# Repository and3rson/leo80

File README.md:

# leo80
Z80-based single-board computer

# Design considerations

- $0000-$7FFF - ROM.
- $8000-$FFFF - RAM.
- Address decoding with ATF16V8.
- Using perfboard for this, so trying to keep it small & simple - will be adding more fancy things later (LCD, UART, etc).
- Simple 8-bit input through '244 tri-state buffer.
- Simple 8-bit output through '273 flip-flop with 8 LEDs for visual output.
- I used AS6C4008 in schematic since it's included in Kicad parts by default. I have various SRAM chips available. Same with W27C512 EPROM.

# Schematic

# PCB

# Resources

- anycpu.org forum [thread](https://anycpu.org/forum/viewtopic.php?f=25&t=1060)
- Original [datasheet](https://www.zilog.com/docs/z80/um0080.pdf) (very slow download), or alternatively - archived versions on [my website](https://dun.ai/files/z80.pdf) and [archive.org](https://archive.org/details/um0080httpswww.zilog.comdocsz80um0080.pdf).
- Z80 interrupt vectors: https://www.smspower.org/Development/InterruptVectors
- SjASMPlus docs: https://z00m128.github.io/sjasmplus/documentation.html

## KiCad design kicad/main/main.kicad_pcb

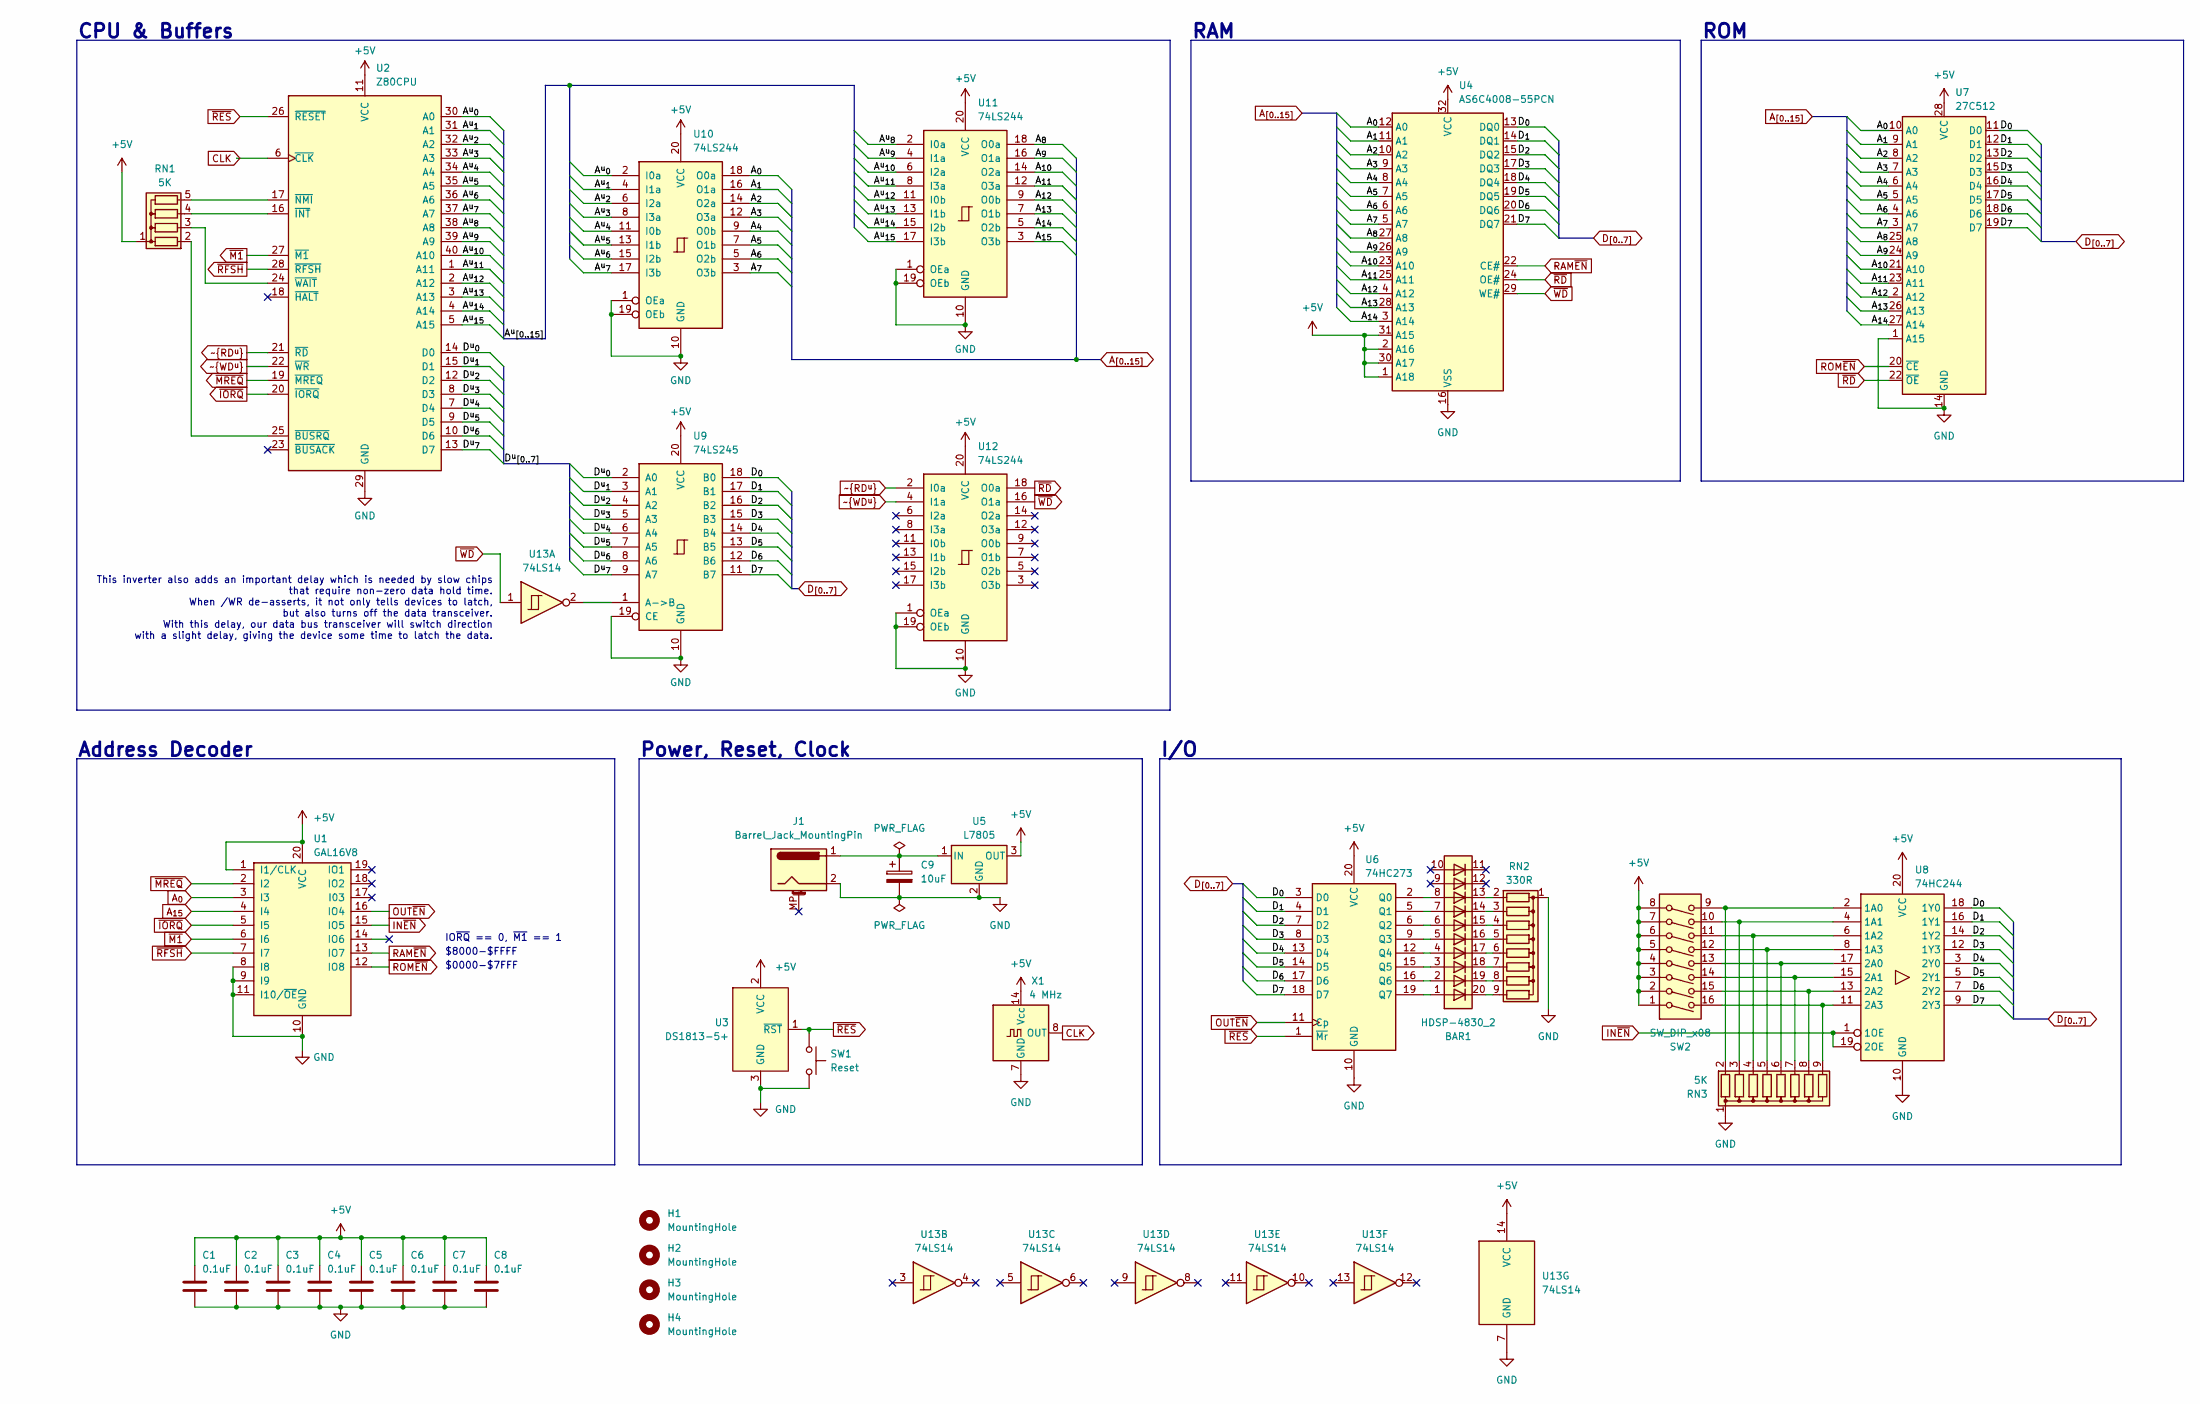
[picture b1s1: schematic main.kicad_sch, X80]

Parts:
BAR1: HDSP-4830_2; HDSP-4830
C1, C3, C4, C6, C7, C8: 0.1uF; C_Disc_Long
C2: 0.1uF; C_Disc_Medium
C5: 0.1uF; C_Disc_D3.0mm_W1.6mm_P2.50mm
C9: 10uF; CP_Radial_D5.0mm_P2.00mm
H1, H2, H3, H4: MountingHole; MountingHole_3.2mm_M3_Pad
J1: Barrel_Jack_MountingPin; BarrelJack_GCT_DCJ200-10-A_Horizontal
RN1: 5K; R_Array_SIP5
RN2: 330R; R_Array_SIP9
RN3: 5K; R_Array_SIP9
SW1: Reset; SW_PUSH_6mm
SW2: SW_DIP_x08; SW_DIP_SPSTx08_Slide_9.78x22.5mm_W7.62mm_P2.54mm
U1: GAL16V8; DIP-20_W7.62mm_Socket
U2: Z80CPU; DIP-40_W15.24mm_Socket
U3: DS1813-5+; TO-92
U4: AS6C4008-55PCN; DIP-32_W15.24mm
U5: L7805; TO-220-3_Vertical
U6: 74HC273; DIP-20_W7.62mm_Socket
U7: 27C512; ZIF28
U8: 74HC244; DIP-20_W7.62mm_Socket
U9: 74LS245; DIP-20_W7.62mm_Socket
U10, U11, U12: 74LS244; DIP-20_W7.62mm_Socket
U13: 74LS14
X1: 4 MHz; Oscillator_DIP-14

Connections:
+5V: C1.1, C2.1, C3.1, C4.1, C5.1, C6.1, C7.1, C8.1, RN1.1 (common), SW2.1, SW2.2, SW2.3, SW2.4, SW2.5, SW2.6, SW2.7, SW2.8, U1.1 (I1/CLK), U1.20 (VCC), U2.11 (VCC), U3.2 (VCC), U4.1 (A18), U4.2 (A16), U4.30 (A17), U4.31 (A15), U4.32 (VCC), U5.3 (OUT), U6.20 (VCC), U7.28 (VCC), U8.20 (VCC), U9.20 (VCC), U10.20 (VCC), U11.20 (VCC), U12.20 (VCC), U13.14 (VCC), X1.14 (Vcc)
/A^{u}_{0}: U2.30 (A0), U10.2 (I0a)
/A^{u}_{1}: U2.31 (A1), U10.4 (I1a)
/A^{u}_{2}: U2.32 (A2), U10.6 (I2a)
/A^{u}_{3}: U2.33 (A3), U10.8 (I3a)
/A^{u}_{4}: U2.34 (A4), U10.11 (I0b)
/A^{u}_{5}: U2.35 (A5), U10.13 (I1b)
/A^{u}_{6}: U2.36 (A6), U10.15 (I2b)
/A^{u}_{7}: U2.37 (A7), U10.17 (I3b)
/A^{u}_{8}: U2.38 (A8), U11.2 (I0a)
/A^{u}_{9}: U2.39 (A9), U11.4 (I1a)
/A^{u}_{10}: U2.40 (A10), U11.6 (I2a)
/A^{u}_{11}: U2.1 (A11), U11.8 (I3a)
/A^{u}_{12}: U2.2 (A12), U11.11 (I0b)
/A^{u}_{13}: U2.3 (A13), U11.13 (I1b)
/A^{u}_{14}: U2.4 (A14), U11.15 (I2b)
/A^{u}_{15}: U2.5 (A15), U11.17 (I3b)
/D^{u}_{0}: U2.14 (D0), U9.2 (A0)
/D^{u}_{1}: U2.15 (D1), U9.3 (A1)
/D^{u}_{2}: U2.12 (D2), U9.4 (A2)
/D^{u}_{3}: U2.8 (D3), U9.5 (A3)
/D^{u}_{4}: U2.7 (D4), U9.6 (A4)
/D^{u}_{5}: U2.9 (D5), U9.7 (A5)
/D^{u}_{6}: U2.10 (D6), U9.8 (A6)
/D^{u}_{7}: U2.13 (D7), U9.9 (A7)
A_{0}: U1.3 (I3), U4.12 (A0), U7.10 (A0), U10.18 (O0a)
A_{1}: U4.11 (A1), U7.9 (A1), U10.16 (O1a)
A_{2}: U4.10 (A2), U7.8 (A2), U10.14 (O2a)
A_{3}: U4.9 (A3), U7.7 (A3), U10.12 (O3a)
A_{4}: U4.8 (A4), U7.6 (A4), U10.9 (O0b)
A_{5}: U4.7 (A5), U7.5 (A5), U10.7 (O1b)
A_{6}: U4.6 (A6), U7.4 (A6), U10.5 (O2b)
A_{7}: U4.5 (A7), U7.3 (A7), U10.3 (O3b)
A_{8}: U4.27 (A8), U7.25 (A8), U11.18 (O0a)
A_{9}: U4.26 (A9), U7.24 (A9), U11.16 (O1a)
A_{10}: U4.23 (A10), U7.21 (A10), U11.14 (O2a)
A_{11}: U4.25 (A11), U7.23 (A11), U11.12 (O3a)
A_{12}: U4.4 (A12), U7.2 (A12), U11.9 (O0b)
A_{13}: U4.28 (A13), U7.26 (A13), U11.7 (O1b)
A_{14}: U4.3 (A14), U7.27 (A14), U11.5 (O2b)
A_{15}: U1.4 (I4), U11.3 (O3b)
CLK: U2.6 (~CLK), X1.8 (OUT)
D_{0}: U4.13 (DQ0), U6.3 (D0), U7.11 (D0), U8.18 (1Y0), U9.18 (B0)
D_{1}: U4.14 (DQ1), U6.4 (D1), U7.12 (D1), U8.16 (1Y1), U9.17 (B1)
D_{2}: U4.15 (DQ2), U6.7 (D2), U7.13 (D2), U8.14 (1Y2), U9.16 (B2)
D_{3}: U4.17 (DQ3), U6.8 (D3), U7.15 (D3), U8.12 (1Y3), U9.15 (B3)
D_{4}: U4.18 (DQ4), U6.13 (D4), U7.16 (D4), U8.3 (2Y0), U9.14 (B4)
D_{5}: U4.19 (DQ5), U6.14 (D5), U7.17 (D5), U8.5 (2Y1), U9.13 (B5)
D_{6}: U4.20 (DQ6), U6.17 (D6), U7.18 (D6), U8.7 (2Y2), U9.12 (B6)
D_{7}: U4.21 (DQ7), U6.18 (D7), U7.19 (D7), U8.9 (2Y3), U9.11 (B7)
GND: C1.2, C2.2, C3.2, C4.2, C5.2, C6.2, C7.2, C8.2, C9.2, J1.2, RN2.1 (common), RN3.1 (common), SW1.2, U1.8 (I8), U1.9 (I9), U1.10 (GND), U1.11 (I10/~OE), U2.29 (GND), U3.3 (GND), U4.16 (VSS), U5.2 (GND), U6.10 (GND), U7.1 (A15), U7.14 (GND), U8.10 (GND), U9.10 (GND), U9.19 (CE), U10.1 (OEa), U10.10 (GND), U10.19 (OEb), U11.1 (OEa), U11.10 (GND), U11.19 (OEb), U12.1 (OEa), U12.10 (GND), U12.19 (OEb), U13.7 (GND), X1.7 (GND)
IN~EN: U1.15 (IO5), U8.1 (1OE), U8.19 (2OE)
unnamed: RN1.2 (R1), U2.25 (~BUSRQ)
unnamed: RN1.3 (R2), U2.24 (~WAIT)
unnamed: RN1.4 (R3), U2.16 (~INT)
unnamed: RN1.5 (R4), U2.17 (~NMI)
unnamed: BAR1.13 (K), RN2.2 (R1)
unnamed: BAR1.14 (K), RN2.3 (R2)
unnamed: BAR1.15 (K), RN2.4 (R3)
unnamed: BAR1.16 (K), RN2.5 (R4)
unnamed: BAR1.17 (K), RN2.6 (R5)
unnamed: BAR1.18 (K), RN2.7 (R6)
unnamed: BAR1.19 (K), RN2.8 (R7)
unnamed: BAR1.20 (K), RN2.9 (R8)
unnamed: RN3.2 (R1), SW2.9, U8.2 (1A0)
unnamed: RN3.3 (R2), SW2.10, U8.4 (1A1)
unnamed: RN3.4 (R3), SW2.11, U8.6 (1A2)
unnamed: RN3.5 (R4), SW2.12, U8.8 (1A3)
unnamed: RN3.6 (R5), SW2.13, U8.17 (2A0)
unnamed: RN3.7 (R6), SW2.14, U8.15 (2A1)
unnamed: RN3.8 (R7), SW2.15, U8.13 (2A2)
unnamed: RN3.9 (R8), SW2.16, U8.11 (2A3)
unnamed: C9.1, J1.1, U5.1 (IN)
unnamed: BAR1.8 (A), U6.2 (Q0)
unnamed: BAR1.7 (A), U6.5 (Q1)
unnamed: BAR1.6 (A), U6.6 (Q2)
unnamed: BAR1.5 (A), U6.9 (Q3)
unnamed: BAR1.4 (A), U6.12 (Q4)
unnamed: BAR1.3 (A), U6.15 (Q5)
unnamed: BAR1.2 (A), U6.16 (Q6)
unnamed: BAR1.1 (A), U6.19 (Q7)
unnamed: U9.1 (A->B), U13.2
OUT~EN: U1.16 (IO4), U6.11 (Cp)
RAM~EN: U1.13 (IO7), U4.22 (CE#)
ROM~EN: U1.12 (IO8), U7.20 (~CE)
~IORQ: U1.5 (I5), U2.20 (~IORQ)
~M1: U1.6 (I6), U2.27 (~M1)
~MREQ: U1.2 (I2), U2.19 (~MREQ)
~RD^{u}: U2.21 (~RD), U12.2 (I0a)
~RD: U4.24 (OE#), U7.22 (~OE), U12.18 (O0a)
~RES: SW1.1, U2.26 (~RESET), U3.1 (~RST), U6.1 (~Mr)
~RFSH: U1.7 (I7), U2.28 (~RFSH)
~WD^{u}: U2.22 (~WR), U12.4 (I1a)
~WD: U4.29 (WE#), U12.16 (O1a), U13.1

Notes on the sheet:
RAM
$8000-$FFFF
Power, Reset, Clock
CPU & Buffers
ROM
IO~{RQ} == 0, ~{M1} == 1
$0000-$7FFF
I/O
Address Decoder
This inverter also adds an important delay which is needed by slow chips that require non-zero data hold time. When /WR de-asserts, it not only tells devices to latch, but also turns off the data transceiver. With this delay, our data bus transceiver will switch direction with a slight delay, givin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

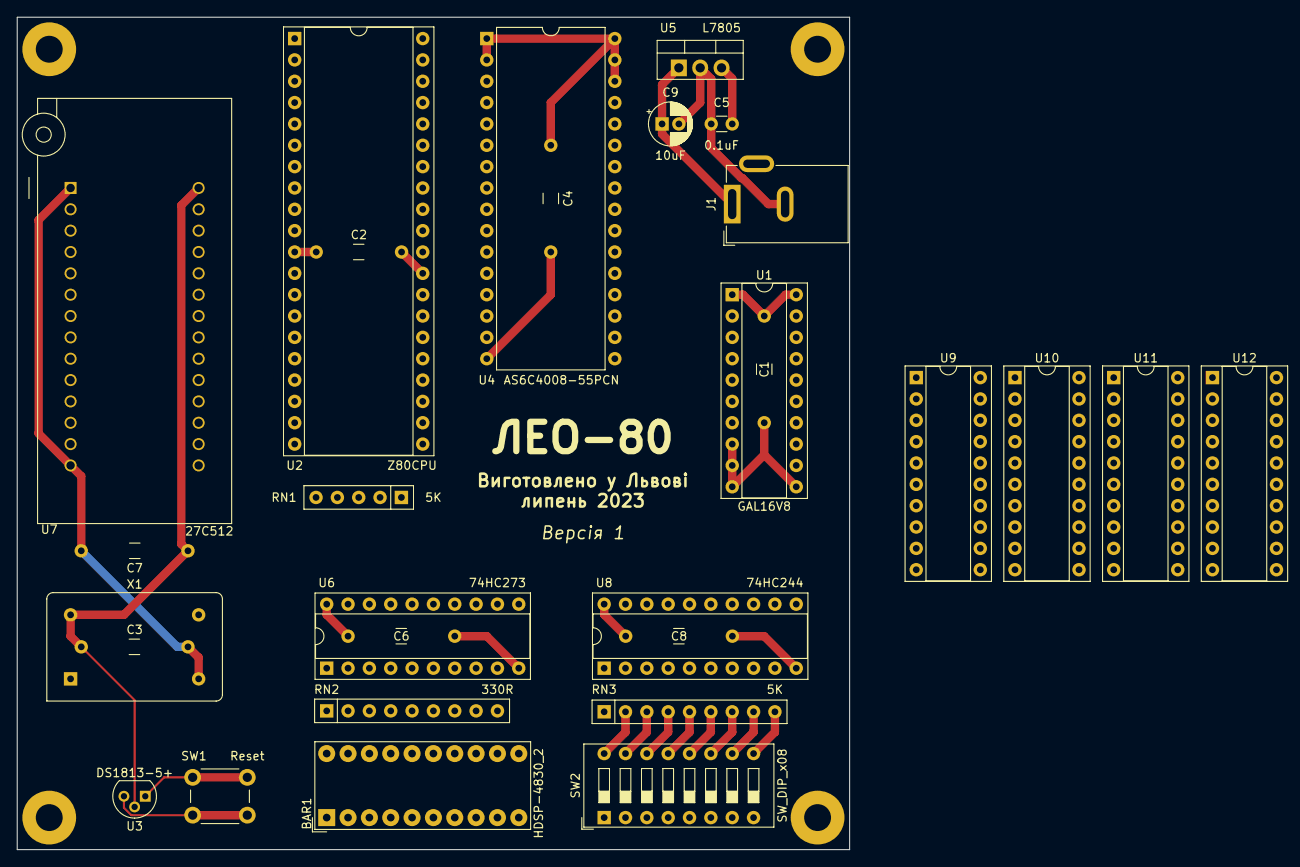
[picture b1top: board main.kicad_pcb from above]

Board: 2 copper layers, 99.1 x 99.1 mm, 33 parts (0 on the bottom side), 93 nets.

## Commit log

2023-07-17 Initial sources
2023-07-17 Add .gitattributes
2023-07-17 Create rom dir
2023-07-17 Add Kicad schematic
2023-07-17 Cleanup
2023-07-18 Smaller KiCad symbols, reset button
2023-07-19 Basic PCB
2023-07-19 First PCB
2023-07-19 Typo
2023-07-19 PCB update + Gerber
2023-07-19 Final v1 PCB
2023-07-19 Update images
2023-07-22 Add sample program (main)
2023-07-24 Add ROM programming rule
2023-07-24 Cleanup main ROM code & Makefile
2023-07-25 Images of build
2023-07-27 Fix RAM CE2, add /RFSH
2023-07-28 Fixes to V1
2023-07-29 Add new buffers
2023-07-29 Add image
